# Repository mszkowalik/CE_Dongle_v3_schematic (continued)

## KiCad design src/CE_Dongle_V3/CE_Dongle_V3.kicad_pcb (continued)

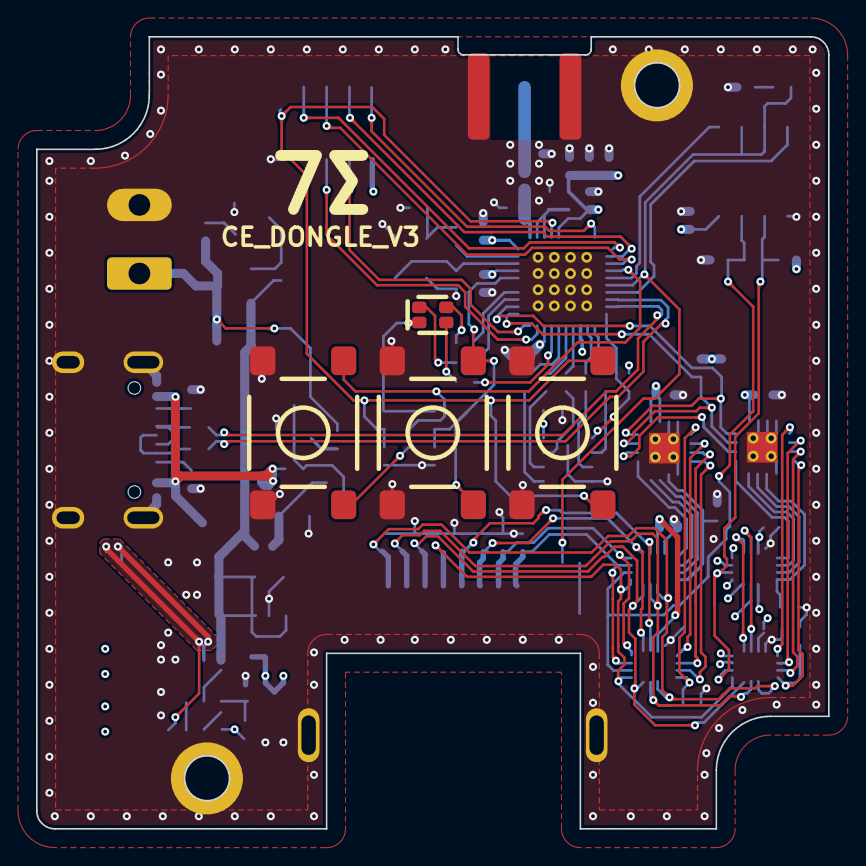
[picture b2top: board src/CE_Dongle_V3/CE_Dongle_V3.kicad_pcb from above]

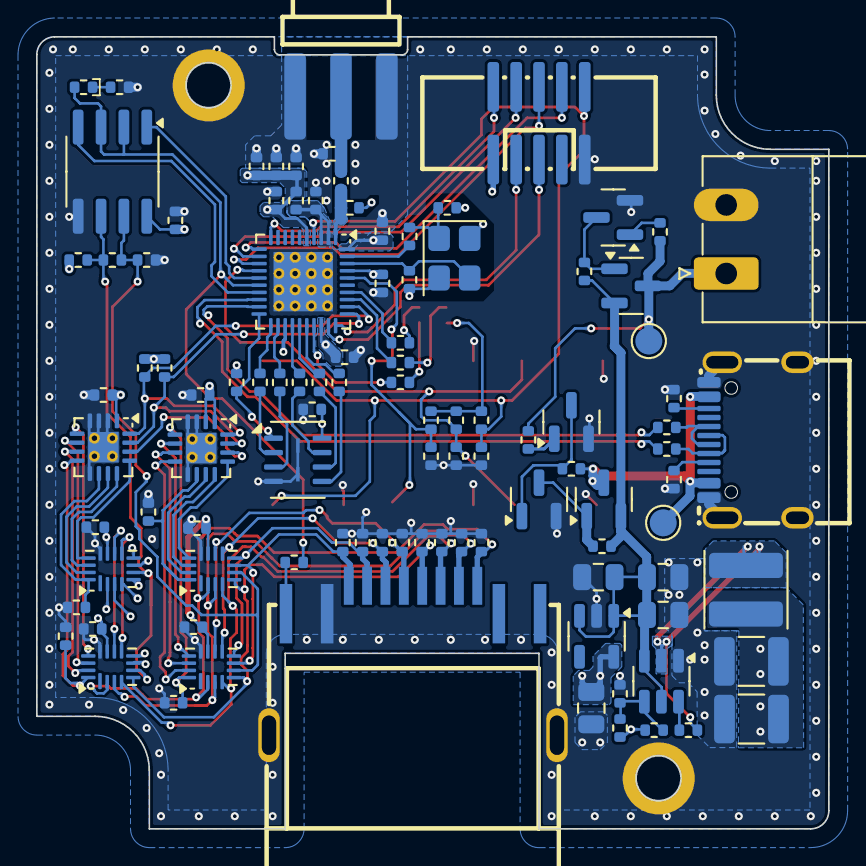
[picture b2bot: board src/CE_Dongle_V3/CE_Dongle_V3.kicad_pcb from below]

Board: 4 copper layers, 44.0 x 44.0 mm, 111 parts (103 on the bottom side), 87 nets.

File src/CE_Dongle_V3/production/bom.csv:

Designator,Footprint,Quantity,Value,LCSC Part #
"C1, C4",0402,2,1uF,C1518208
"C10, C11, C19, C24, C25, C26, C27, C28, C29, C30, C31, C32, C6, C7, C8, C9",0402,16,100nF,C1525
"C12, C13",0402,2,10uF,C315248
"C14, C15",0402,2,1.2pF,C76899
"C16, C17",0402,2,12pF,C106201
"C18, C20, C33, C34, C35, C36, C37, C38, C39",0402,9,100pF,C106200
"C2, C21, C22, C23",0805,4,10uF,C440198
"C3, C5",1210,2,47uF,C5440143
D2,0402,1,LTST-C281KRKT,C364556
D7,LED-SMD_4P-L1.6-W1.5-BR,1,XL-3227SURUGC,C965840
G2,1551RFLGY,1,Hammond_1551RFLGY,
J1,USB-3.1-SMD_U262-161N-4BVC11,1,USB_C_Receptacle_USB2.0_16P,C319148
J2,RJ45-TH_RC01812,1,8P8C_LED_Shielded,C708645
J3,SMA-SMD_BWSMA-KE-P001,1,Conn_Coaxial,C496550
J4,IDC-SMD_10P-P1.27-3220-10-0300-00,1,Conn_02x05_Odd_Even,C42372555
J5,"PhoenixContact_MC_1,5_2-G-3.81_1x02_P3.81mm_Horizontal",1,Conn_01x02,C8387
J6,TerminalBlock_Plug_Invisible,1,WJ15EDGK-3.81-2P,C8466
"L1, L2",0402,2,2.2nH,C91240
L4,L_Changjiang_FTC404030S,1,4.7uH,C39676083
"Q1, Q2",SOT-23,2,AO3401A,C15127
"Q3, Q4, Q5",SOT-23,3,BC817-40-7-F,C435867
"R1, R19, R23, R24, R30, R5",0402,6,120R,C25079
"R10, R11",0402,2,22R,C25092
"R12, R13, R15, R16, R17",0402,5,100R,C25076
R18,0402,1,0R,C17168
R2,0402,1,22K,C25768
"R21, R22, R37, R38, R39, R40, R44",0402,7,10K,C25744
"R25, R26, R27, R28, R29, R41",0402,6,100K,C25741
"R3, R4",0402,2,1K,C11702
"R42, R43, R8, R9",0402,4,5K1,C25905
"SW_BOOT1, SW_RST1, SW_USR1",SW-SMD_4P-L6.0-W6.0-P4.50-LS9.0-H4.3,3,KH-6X6X4.3H-STM,C2837530
"TP1, TP2",TestPoint_Pad_D1.5mm,2,TestPoint,
U1,VQFN-40-1EP_5x5mm_P0.4mm_EP3.3x3.3mm_ThermalVias,1,ESP32-C6,C5364646
"U10, U7, U8, U9",UQFN-16_1.8x2.6mm_P0.4mm,4,TMUX1208QRSVRQ1,C2876797
U11,SOT-23-5,1,TPS70950DBVR,C96028
U2,SOIC-8_3.9x4.9mm_P1.27mm,1,SP3485,C8963
U3,Winbond_USON-8-2EP_3x4mm_P0.8mm_EP0.2x0.8mm,1,W25Q64JWUUIQ,C6604692
U4,SOT-23-6,1,TPS54302DDCR,C311983
"U5, U6",QFN-16-1EP_3x3mm_P0.5mm_EP1.7x1.7mm_ThermalVias,2,PCF8574RGTR(UMW),C22396384
Y1,Crystal_SMD_3225-4Pin_3.2x2.5mm,1,40MHz,C37635390

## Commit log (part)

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2025-10-17 INIT
2025-10-18 layout cont. corrected some wrong net names
2025-10-18 layout finished
2025-11-10 schematic update before production
2025-11-10 cleaned up repo structure
2026-05-01 V3.1 first changes
2026-05-09 ongoing work
2026-06-02 Layout progress
2026-06-03 floorplan changed, check in
2026-06-04 PCB layout continued
2026-06-09 pcb work continued
2026-06-09 schematic cleanup, verification. GPIO9 pin pulldown changed to pullup.
